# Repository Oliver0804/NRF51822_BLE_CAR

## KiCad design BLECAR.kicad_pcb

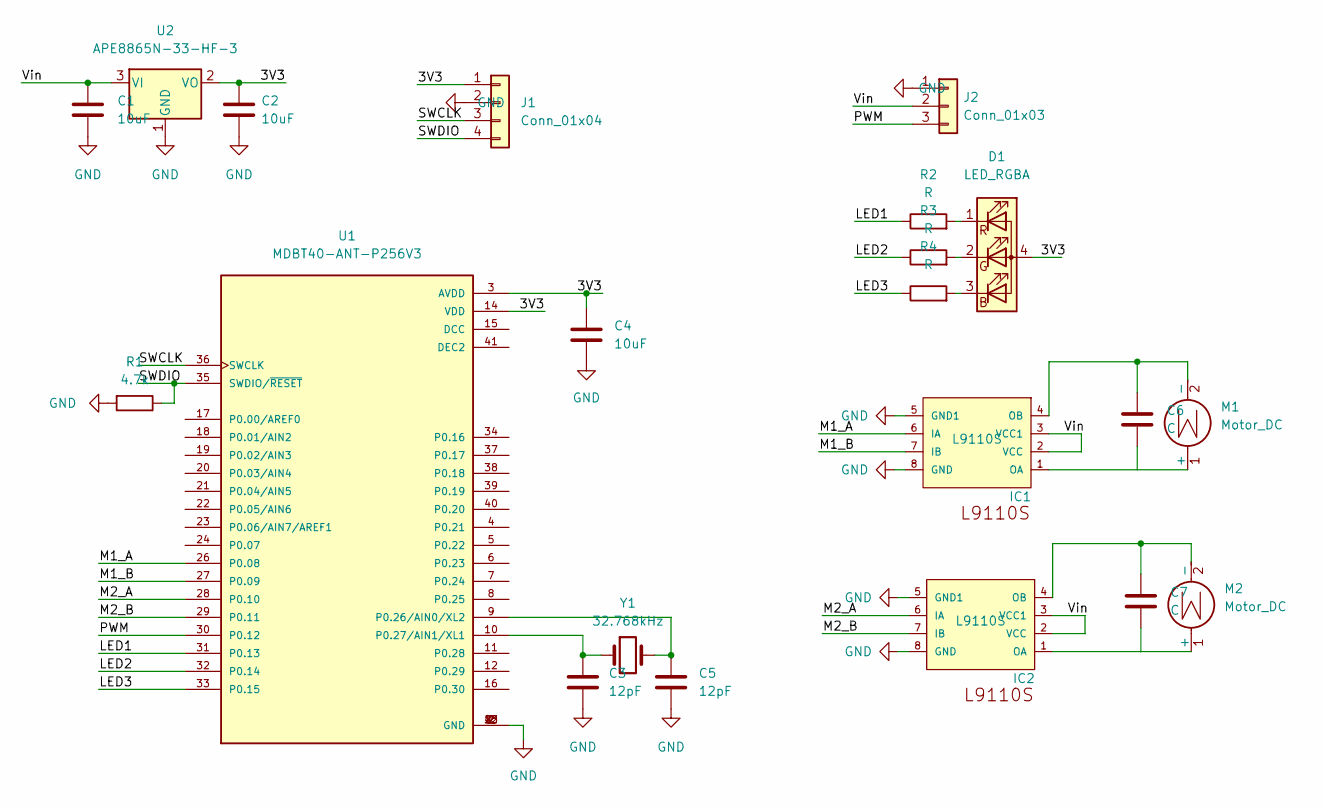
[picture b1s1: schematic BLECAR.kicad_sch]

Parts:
C1, C2, C4: 10uF; C_0603_1608Metric
C3, C5: 12pF; C_0402_1005Metric
C6, C7: C; C_0603_1608Metric
D1: LED_RGBA; LED_LiteOn_LTST-C19HE1WT
IC1, IC2: L9110S; SOIC-8_3.9x4.9mm_P1.27mm
J1: Conn_01x04; PinHeader_1x04_P1.27mm_Vertical
J2: Conn_01x03; PinHeader_1x03_P1.27mm_Vertical
M1, M2: Motor_DC; PinHeader_1x02_P1.27mm_Vertical
R1: 4.7k; R_0402_1005Metric
R2, R3, R4: R; R_0402_1005Metric
U1: MDBT40-ANT-P256V3; MODULE_MDBT40-ANT-P256V3
U2: APE8865N-33-HF-3; SOT-23
Y1: 32.768kHz; Crystal_SMD_3215-2Pin_3.2x1.5mm

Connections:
/3V3: C2.1, C4.1, D1.4 (A), J1.1, U1.3 (AVDD), U1.14 (VDD), U2.2 (VO)
/LED1: R2.1, U1.31 (P0.13)
/LED2: R3.1, U1.32 (P0.14)
/LED3: R4.1, U1.33 (P0.15)
/M1_A: IC1.6 (IA), U1.26 (P0.08)
/M1_B: IC1.7 (IB), U1.27 (P0.09)
/M2_A: IC2.6 (IA), U1.28 (P0.10)
/M2_B: IC2.7 (IB), U1.29 (P0.11)
/PWM: J2.3, U1.30 (P0.12)
/SWCLK: J1.3, U1.36 (SWCLK)
/SWDIO: J1.4, R1.1, U1.35 (SWDIO/~RESET)
/Vin: C1.1, IC1.2 (VCC), IC1.3 (VCC1), IC2.2 (VCC), IC2.3 (VCC1), J2.2, U2.3 (VI)
GND: C1.2, C2.2, C3.2, C4.2, C5.2, IC1.5 (GND1), IC1.8 (GND), IC2.5 (GND1), IC2.8 (GND), J1.2, J2.1, R1.2, U1.1 (GND), U1.2 (GND), U1.13 (GND), U1.25 (GND), U1.42 (GND), U2.1 (GND)
unnamed: C3.1, U1.10 (P0.27/AIN1/XL1), Y1.1
unnamed: C5.1, U1.9 (P0.26/AIN0/XL2), Y1.2
unnamed: C6.1, IC1.4 (OB), M1.2 (-)
unnamed: C7.1, IC2.4 (OB), M2.2 (-)
unnamed: D1.1 (RK), R2.2
unnamed: D1.2 (GK), R3.2
unnamed: D1.3 (BK), R4.2
unnamed: IC1.1 (OA), M1.1 (+)
unnamed: IC2.1 (OA), M2.1 (+)

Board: 2 copper layers, 21 parts (15 on the bottom side), 22 nets, no tracks yet.
